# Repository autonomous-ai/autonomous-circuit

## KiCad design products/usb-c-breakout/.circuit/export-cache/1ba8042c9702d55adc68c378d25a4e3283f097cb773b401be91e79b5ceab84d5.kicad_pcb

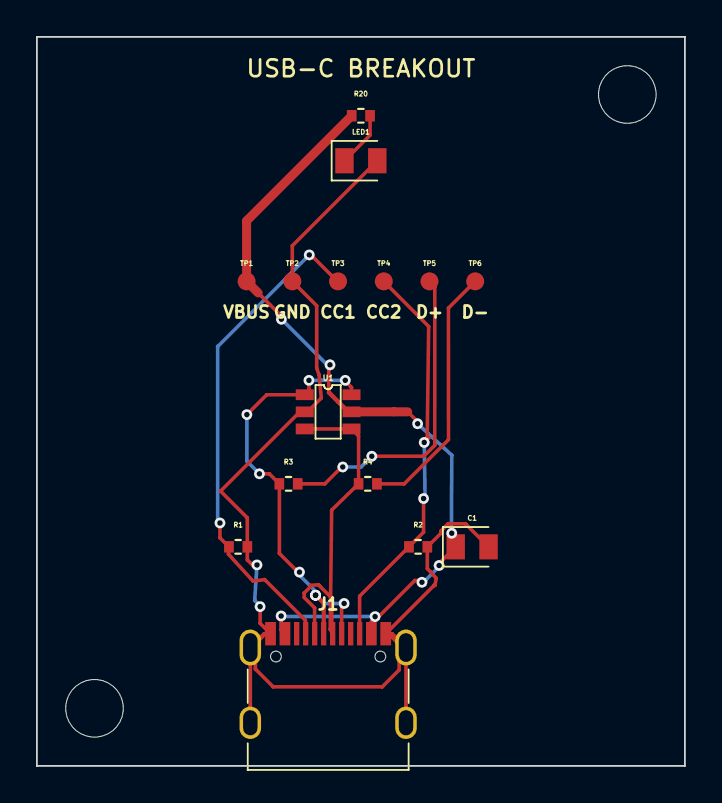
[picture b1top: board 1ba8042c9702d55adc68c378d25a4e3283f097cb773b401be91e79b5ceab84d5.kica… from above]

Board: 2 copper layers, 36.0 x 40.5 mm, 15 parts (0 on the bottom side), 9 nets.

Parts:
C1: 10uF; capacitor_cap0805
J1: J1; TYPE-C-31-M-12
LED1: LED; led_0805_color(green)
R1, R2: 5.1kΩ; resistor_res0402
R3, R4: 27Ω; resistor_res0402
R20: 1kΩ; resistor_res0402
TP1: TP1; test_point_smtpad_circle_d1
TP2: TP2; test_point_smtpad_circle_d1
TP3: TP3; test_point_smtpad_circle_d1
TP4: TP4; test_point_smtpad_circle_d1
TP5: TP5; test_point_smtpad_circle_d1
TP6: TP6; test_point_smtpad_circle_d1
U1: USBLC6-2SC6

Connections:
.J1 > .CC1 to .R1 > .pin1: J1.6, R1.1, TP3.1
.J1 > .CC2 to .R2 > .pin1: J1.12, R2.1, TP4.1
.R20 > .pin2 to .LED1 > .anode: LED1.1, R20.2
GND: C1.2, J1.1, J1.2, J1.3, J1.4, J1.13, J1.14, LED1.2, R1.2, R2.2, TP2.1, U1.2
USB_DM: R4.2, TP6.1
USB_DM_CONN: J1.7, J1.9, R4.1, U1.3, U1.4
USB_DP: R3.2, TP5.1
USB_DP_CONN: J1.8, J1.10, R3.1, U1.1, U1.6
V5: C1.1, J1.15, J1.16, R20.1, TP1.1, U1.5
